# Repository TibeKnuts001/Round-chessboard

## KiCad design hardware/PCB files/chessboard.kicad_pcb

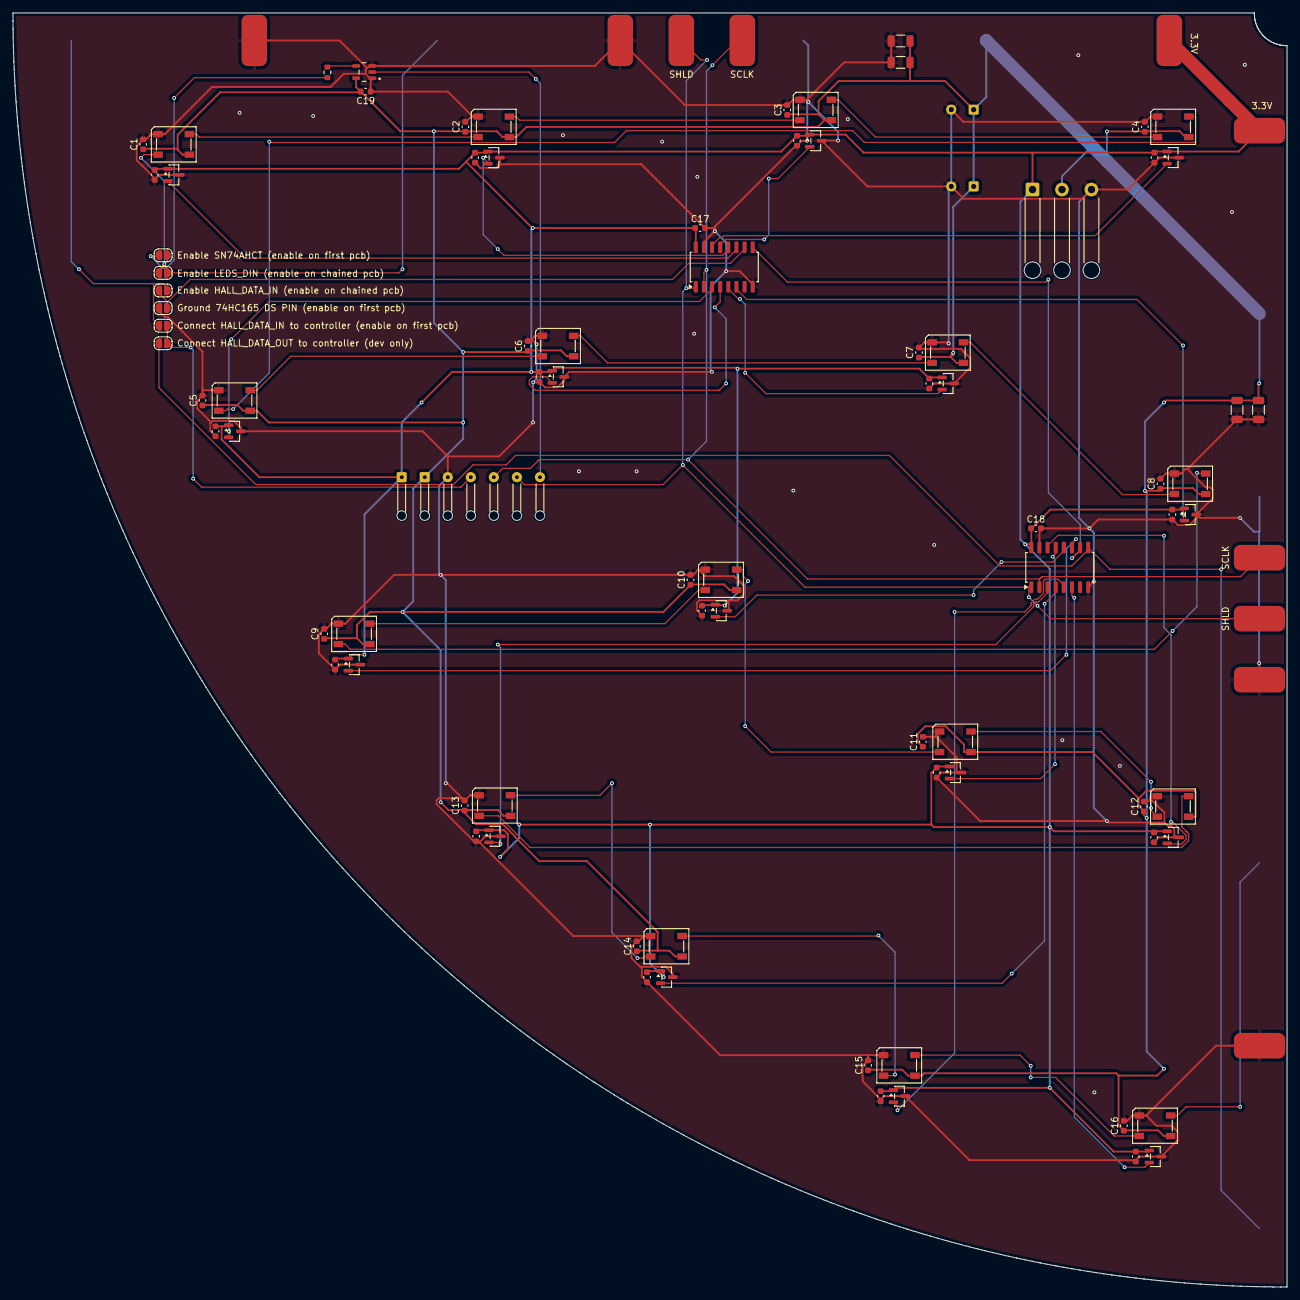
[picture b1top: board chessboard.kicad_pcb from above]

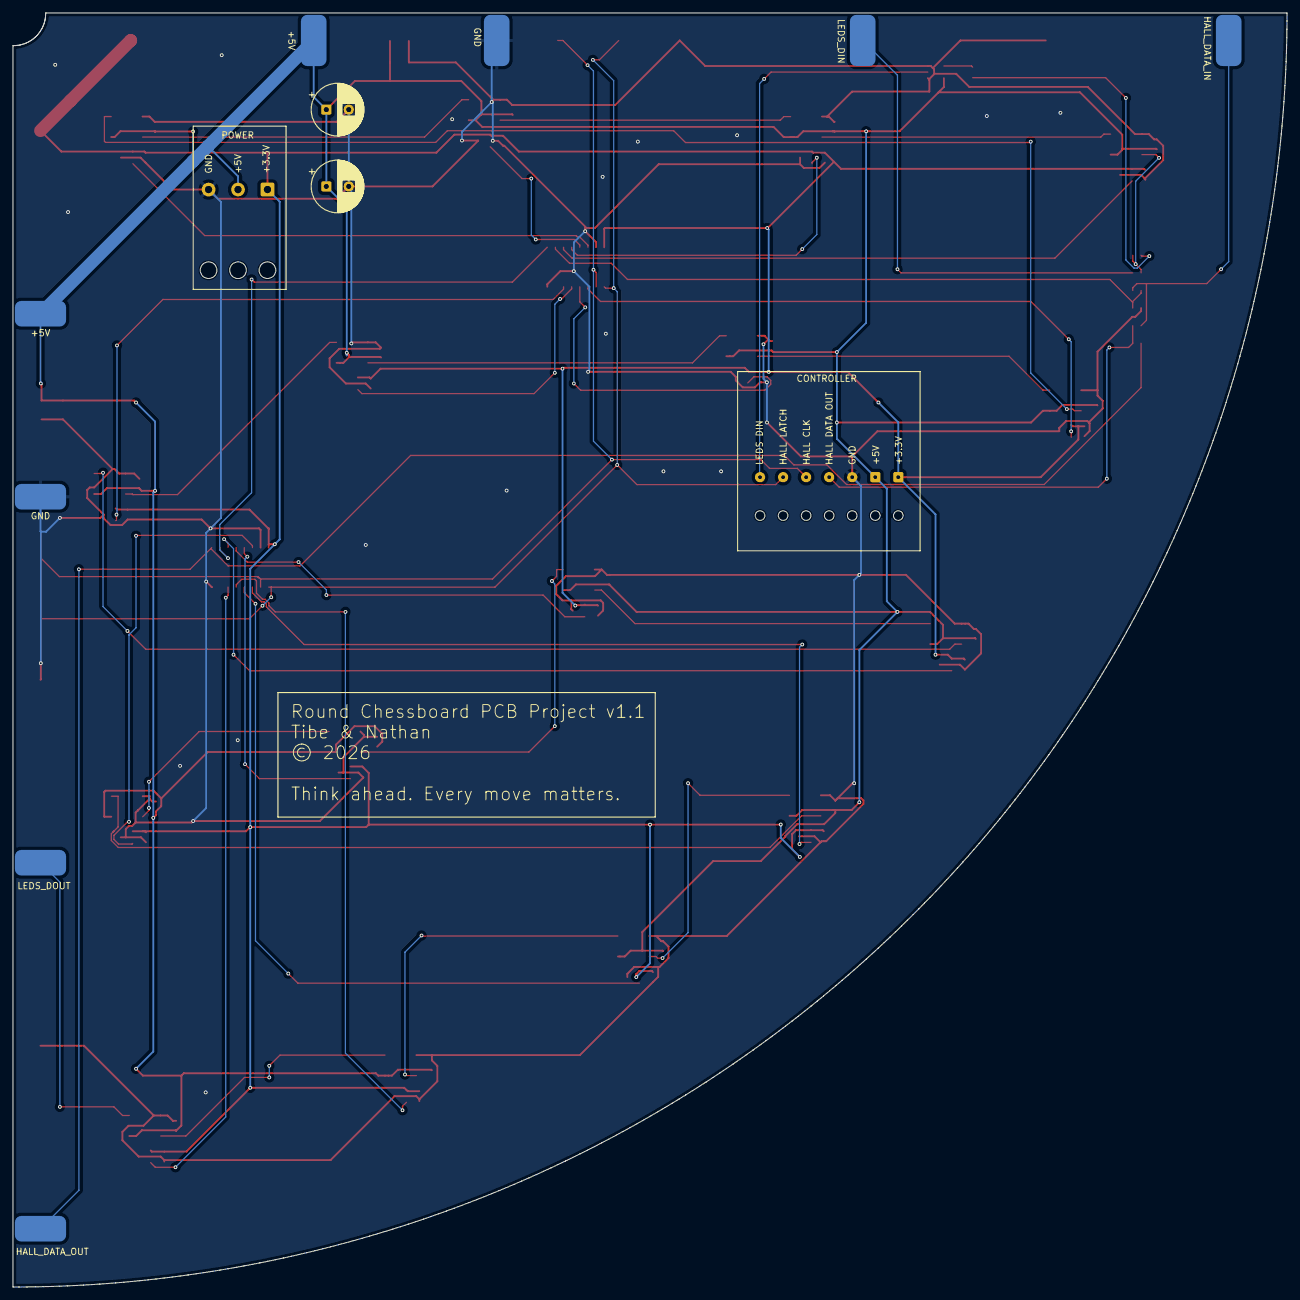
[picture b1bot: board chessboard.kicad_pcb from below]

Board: 2 copper layers, 199.0 x 199.0 mm, 103 parts (10 on the bottom side), 47 nets.

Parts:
C1, C2, C3, C4, C5, C6, C7, C8, C9, C10, C11, C12, C13, C14, C15, C16, C17, C18, C19, C20, C21, C22, C23, C24, C25, C26, C27, C28, C29, C30, C31, C32, C33, C34, C35: 100nF; C_0603_1608Metric
C36, C37, C38, C39: 22uF; C_1206_3216Metric
C40, C41: Optional capacitor; CP_Radial_D8.0mm_P3.50mm
D1, D2, D3, D4, D5, D6, D7, D8, D9, D10, D11, D12, D13, D14, D15, D16: SK5812; LED_SK6812_PLCC4_5.0x5.0mm_P3.2mm
H1, H2, H3, H4: SC2063SO-TR; SOT-23
J1: POWER; SolderWire-0.5sqmm_1x03_P4.6mm_D0.9mm_OD2.1mm_Relief
J2, J19: SHLD; SolderWirePad_1x01_SMD_4x8mm
J3: LEDS_DIN; SolderWirePad_1x01_SMD_4x8mm
J4: HALL_DATA_IN; SolderWirePad_1x01_SMD_4x8mm
J5, J7: +5V; SolderWirePad_1x01_SMD_4x8mm
J6, J8: GND; SolderWirePad_1x01_SMD_4x8mm
J9: LEDS_DOUT; SolderWirePad_1x01_SMD_4x8mm
J10: HALL_DATA_OUT; SolderWirePad_1x01_SMD_4x8mm
J11: CONTROLLER; SolderWire-0.1sqmm_1x06_P3.6mm_D0.4mm_OD1mm_Relief_1__SCHAA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
J12: PCB_CNNT1; SolderWirePad_1x01_SMD_4x8mm
J13: PCB_CNNT2; SolderWirePad_1x01_SMD_4x8mm
J14: PCB_CNNT3; SolderWirePad_1x01_SMD_4x8mm
J15: PCB_CNNT4; SolderWirePad_1x01_SMD_4x8mm
J16, J17: +3.3V; SolderWirePad_1x01_SMD_4x8mm
J18, J20: SCLK; SolderWirePad_1x01_SMD_4x8mm
JP1: Enable LEDS_DIN (enable on chained pcb); SolderJumper-2_P1.3mm_Open_RoundedPad1.0x1.5mm
JP2: Enable SN74AHCT (enable on first pcb); SolderJumper-2_P1.3mm_Open_RoundedPad1.0x1.5mm
JP3: Enable HALL_DATA_IN (enable on chained pcb); SolderJumper-2_P1.3mm_Open_RoundedPad1.0x1.5mm
JP4: Ground 74HC165 DS PIN (enable on first pcb); SolderJumper-2_P1.3mm_Open_RoundedPad1.0x1.5mm
JP5: Connect HALL_DATA_IN to controller (enable on fir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; SolderJumper-2_P1.3mm_Open_RoundedPad1.0x1.5mm
JP6: Connect HALL_DATA_OUT to controller (dev only); SolderJumper-2_P1.3mm_Open_RoundedPad1.0x1.5mm
R1: 330 Ohm; R_0603_1608Metric
U5, U6, U7, U8, U9, U10, U11, U12, U13, U14, U15, U16: SC2063SO-TR; SOT-23
U17, U18: 74HC165; SOP-16_4.4x10.4mm_P1.27mm
U19: SN74AHCT1G125DBVR; SOT95P280X145-5N

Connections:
+3.3V: C17.1, C18.1, C20.1, C21.1, C22.1, C23.1, C24.1, C25.1, C26.1, C27.1, C28.1, C29.1, C30.1, C31.1, C32.1, C33.1, C34.1, C35.1, H1.1 (V_{CC}), H2.1 (V_{CC}), H3.1 (V_{CC}), H4.1 (V_{CC}), J1.1, J11.1, J16.1, J17.1, U5.1 (V_{CC}), U6.1 (V_{CC}), U7.1 (V_{CC}), U8.1 (V_{CC}), U9.1 (V_{CC}), U10.1 (V_{CC}), U11.1 (V_{CC}), U12.1 (V_{CC}), U13.1 (V_{CC}), U14.1 (V_{CC}), U15.1 (V_{CC}), U16.1 (V_{CC}), U17.16 (VCC), U18.16 (VCC)
+5V: C1.1, C2.1, C3.1, C4.1, C5.1, C6.1, C7.1, C8.1, C9.1, C10.1, C11.1, C12.1, C13.1, C14.1, C15.1, C16.1, C19.2, C36.1, C37.1, C38.1, C39.1, C40.1, C41.1, D1.3 (VDD), D2.3 (VDD), D3.3 (VDD), D4.3 (VDD), D5.3 (VDD), D6.3 (VDD), D7.3 (VDD), D8.3 (VDD), D9.3 (VDD), D10.3 (VDD), D11.3 (VDD), D12.3 (VDD), D13.3 (VDD), D14.3 (VDD), D15.3 (VDD), D16.3 (VDD), J1.2, J5.1, J7.1, J11.2, U19.5 (VCC)
GND: C1.2, C2.2, C3.2, C4.2, C5.2, C6.2, C7.2, C8.2, C9.2, C10.2, C11.2, C12.2, C13.2, C14.2, C15.2, C16.2, C17.2, C18.2, C19.1, C20.2, C21.2, C22.2, C23.2, C24.2, C25.2, C26.2, C27.2, C28.2, C29.2, C30.2, C31.2, C32.2, C33.2, C34.2, C35.2, C36.2, C37.2, C38.2, C39.2, C40.2, C41.2, D1.1 (VSS), D2.1 (VSS), D3.1 (VSS), D4.1 (VSS), D5.1 (VSS), D6.1 (VSS), D7.1 (VSS), D8.1 (VSS), D9.1 (VSS), D10.1 (VSS), D11.1 (VSS), D12.1 (VSS), D13.1 (VSS), D14.1 (VSS), D15.1 (VSS), D16.1 (VSS), H1.3 (GND), H2.3 (GND), H3.3 (GND), H4.3 (GND), J1.3, J6.1, J8.1, J11.3, J12.1, J13.1, J14.1, J15.1, JP4.1 (A), U5.3 (GND), U6.3 (GND), U7.3 (GND), U8.3 (GND), U9.3 (GND), U10.3 (GND), U11.3 (GND), U12.3 (GND), U13.3 (GND), U14.3 (GND), U15.3 (GND), U16.3 (GND), U17.8 (GND), U17.15 (~CE), U18.8 (GND), U18.15 (~CE), U19.1 (~OE), U19.3 (GND)
HALL_DATA_IN: J4.1, JP3.2 (B), JP5.1 (A)
HALL_DATA_OUT: J10.1, JP6.1 (A), U18.9 (Q7)
HALL_SENSOR1: H1.2 (V_{OUT}), U17.11 (D0)
HALL_SENSOR2: H2.2 (V_{OUT}), U17.12 (D1)
HALL_SENSOR3: H3.2 (V_{OUT}), U17.13 (D2)
HALL_SENSOR4: H4.2 (V_{OUT}), U17.14 (D3)
HALL_SENSOR5: U5.2 (V_{OUT}), U17.3 (D4)
HALL_SENSOR6: U6.2 (V_{OUT}), U17.4 (D5)
HALL_SENSOR7: U7.2 (V_{OUT}), U17.5 (D6)
HALL_SENSOR8: U8.2 (V_{OUT}), U17.6 (D7)
HALL_SENSOR9: U9.2 (V_{OUT}), U18.11 (D0)
HALL_SENSOR10: U10.2 (V_{OUT}), U18.12 (D1)
HALL_SENSOR11: U11.2 (V_{OUT}), U18.13 (D2)
HALL_SENSOR12: U12.2 (V_{OUT}), U18.14 (D3)
HALL_SENSOR13: U13.2 (V_{OUT}), U18.3 (D4)
HALL_SENSOR14: U14.2 (V_{OUT}), U18.4 (D5)
HALL_SENSOR15: U15.2 (V_{OUT}), U18.5 (D6)
HALL_SENSOR16: U16.2 (V_{OUT}), U18.6 (D7)
LEDS_DIN: J3.1, JP1.2 (B)
LEDS_DOUT: D16.4 (DOUT), J9.1
unnamed: D1.2 (DIN), JP1.1 (A), JP2.2 (B)
unnamed: D1.4 (DOUT), D2.2 (DIN)
unnamed: D2.4 (DOUT), D3.2 (DIN)
unnamed: D3.4 (DOUT), D4.2 (DIN)
unnamed: D4.4 (DOUT), D5.2 (DIN)
unnamed: D5.4 (DOUT), D6.2 (DIN)
unnamed: D6.4 (DOUT), D7.2 (DIN)
unnamed: D7.4 (DOUT), D8.2 (DIN)
unnamed: D8.4 (DOUT), D9.2 (DIN)
unnamed: D9.4 (DOUT), D10.2 (DIN)
unnamed: D10.4 (DOUT), D11.2 (DIN)
unnamed: D11.4 (DOUT), D12.2 (DIN)
unnamed: D12.4 (DOUT), D13.2 (DIN)
unnamed: D13.4 (DOUT), D14.2 (DIN)
unnamed: D14.4 (DOUT), D15.2 (DIN)
unnamed: D15.4 (DOUT), D16.2 (DIN)
unnamed: JP2.1 (A), R1.1
unnamed: JP3.1 (A), JP4.2 (B), U17.10 (DS)
unnamed: U17.9 (Q7), U18.10 (DS)
unnamed: R1.2, U19.4 (Y)
RPI-GPIO-LEDS: J11.7, U19.2 (A)
RPI-GPIO-MISO: J11.4, JP5.2 (B), JP6.2 (B)
RPI-GPIO-SCLK: J11.5, J18.1, J20.1, U17.2 (CP), U18.2 (CP)
RPI-GPIO-SHLD: J2.1, J11.6, J19.1, U17.1 (~PL), U18.1 (~PL)

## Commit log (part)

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2026-02-06 Initial work
2026-02-06 Refactored and basic checkers support
2026-02-06 Working checkers
2026-02-06 Checkers ok?
2026-02-06 pretty good version
2026-02-06 better version
2026-02-06 Installed updates
2026-02-06 Nog betere versie
2026-02-06 Bijna final?
2026-02-06 beste versie tot nu toe
2026-02-06 Screensaver
2026-02-06 icons chanaged + bugfix in checkers
2026-02-07 removed autostart + small fixes
2026-02-07 Performance improvements 55% CPU down to 3-4%
2026-02-07 Performance improvements in screensaver 30-15FPS = 80->40% CPU
2026-02-07 Screensaver audio fixed
2026-02-07 Screensaver audio toggle in general settings
2026-02-07 Undo feature added
2026-02-07 Stockfish think time is now max think time
2026-02-07 validate board state werk met effecten
2026-02-07 valdiate board state zit in main game loop
2026-02-07 je kan spelen terwijl validite board state aan stat
2026-02-07 temp messages gefixed
2026-02-07 worstfish toegevoegd
2026-02-07 added pawn promotion
2026-02-14 Deze dingen werken nu: assisted setup messages casteling prev move lights checkers bug met pawn promotion
2026-02-14 removed the no legal move msg
2026-02-14 rotated board
2026-02-16 stockfish + rotate board
2026-02-16 updates voor RPi5
2026-02-16 Working on RPi5
2026-02-16 Latest updates
2026-02-16 added sound effects
2026-02-16 board mismatch when extra pieces
2026-02-16 fixed bugs
2026-02-16 bug fix nummer zoveel
2026-02-17 fixed checkers ai sliders
2026-02-17 castel leds
2026-02-17 checkers fixed for rpi 3
2026-02-17 more led effects
2026-02-17 random idle music
2026-02-17 addded the tutorial
2026-02-17 fixt tutorial on checlers
2026-02-17 test
2026-02-17 removed old
2026-02-17 update script
2026-02-17 update.sh update
2026-02-17 update.sh update 2
2026-02-17 update geupdate
2026-02-17 updating update
2026-02-17 changed "update now" to "update"
2026-02-17 changed update modals
2026-02-17 updated it again
2026-02-17 update availaable update
2026-02-17 assisted setup for any board
2026-02-17 removed coordinates
2026-02-17 fixed assisted setup
2026-03-06 fixed checkers always displaying "Turn: white"
2026-03-06 fixed stopping tutoriol turning on the idle effects and ending setup stopping game
2026-03-06 enhanced game over detection and LED feedback for checkmate and wins
2026-03-06 add piece image key retrieval for checkers and chess, enhance assisted setup notifications
2026-03-06 add sound settings: implement effects and music volume controls with sliders
2026-03-06 add hide board display feature: implement toggle for chess and checkers to hide board and highlights
2026-03-06 Add color selection dialog for Checkers and Chess games
    - Introduced a color selection dialog in both CheckersGUI and ChessGUI to allow players to choose their sides before starting a new game.
    - Added logic to handle the orientation of the board based on the selected color.
    - Updated the rendering of the game board to rotate correctly depending on the player's choice.
    - Implemented functionality for AI to choose a color when playing against the computer.
    - Added a switch icon for swapping colors in the dialog.
    - Included a new asset for the switch icon used in the color selection dialog.
2026-03-08 fixed bug where if in checkers a multi-capture has exactly 2 intermediate squares it thinks it did a castle
2026-03-08 fixed intermiated leds not showing for checker AI move
2026-03-08 fixed bug where pieces were rotated incorrectly on screen
2026-03-08 Enhance AI color selection: add toggle for AI opponent color in Checkers and Chess color selection menu
2026-03-11 Implement secret debug tab unlock gesture, updated settings and more
2026-03-11 Create pictures
2026-03-11 Initial plan
2026-03-11 Create pictures and 3D files folders
2026-03-11 test uploading large pictures
2026-03-11 deleted test
2026-03-11 Added checker's 3D files
2026-03-11 Remove empty .gitkeep files from 3D files and pictures directories
2026-03-12 Add checkers win sound effect
2026-03-13 feat: Add base HTML template and index page for draughts game
    - Created a base HTML template (`base.html`) for consistent layout across pages.
    - Developed an index page (`index.html`) that extends the base template, featuring game controls, board area, and move list.
    - Integrated Bootstrap 5.3 for styling and layout.
    - Added jQuery for game logic support.
    feat: Implement SVG rendering for draughts boards
    - Introduced `svg.py` for rendering draughts boards as SVG images.
2026-03-13 feat: Implement checkers variant selection and settings integration
2026-03-13 Add support for switching between chess and checkers games with exit confirmation dialog updates
2026-03-13 feat: Enhance update process with waiting status and countdown before restart
2026-03-13 chore: untrack .vscode/ from git
2026-03-13 chore: untrack .copilot_summary.txt from git
2026-03-13 chore: ignore .copilot_summary.txt
2026-03-13 moved files

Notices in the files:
hardware/PCB files/chessboard.kicad_pcb:
© 2026
